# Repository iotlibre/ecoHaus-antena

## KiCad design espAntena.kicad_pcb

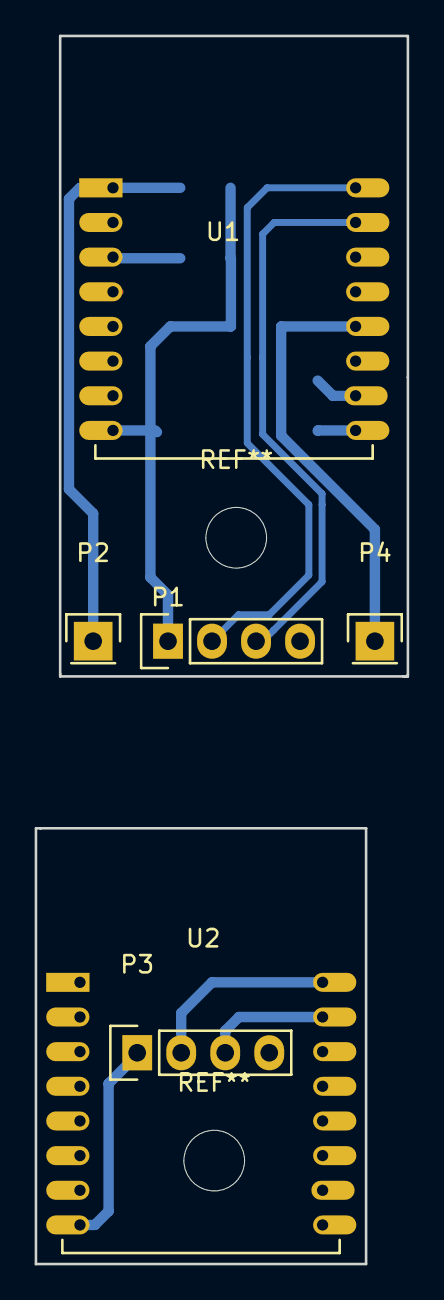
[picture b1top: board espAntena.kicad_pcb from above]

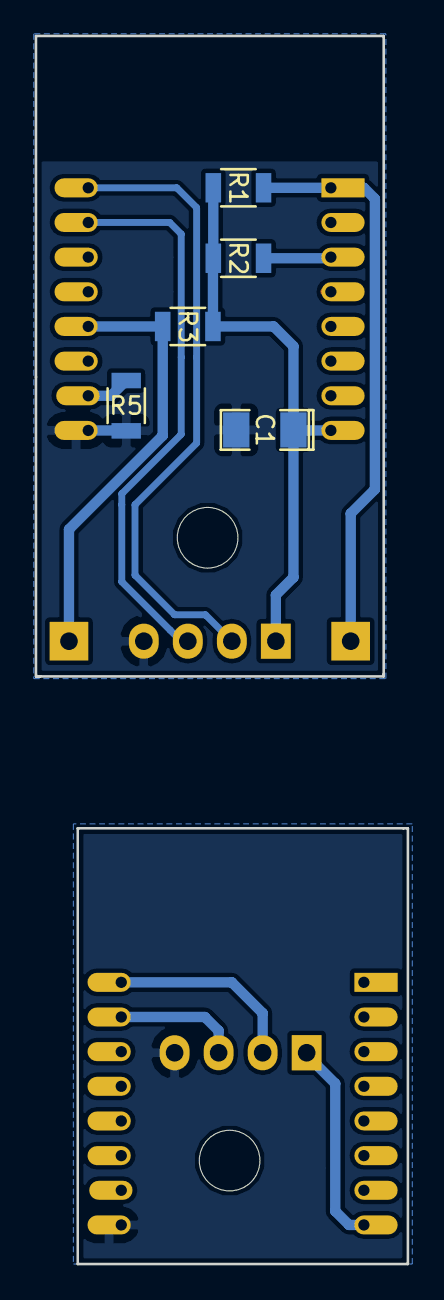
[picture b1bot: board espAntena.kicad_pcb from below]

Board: 2 copper layers, 21.5 x 70.9 mm, 11 parts (5 on the bottom side), 11 nets.

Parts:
C1: 100nF; SMD-1206_Pol
P1, P3: CONN_01X04; Socket_Strip_Straight_1x04
P2, P4: CONN_01X01; Pin_Header_Straight_1x01
R1, R2, R3: 10KR; R_1206
R5: 10kR; R_1206
U1, U2: ESP-12E

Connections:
GND: C1.2, P1.4, P3.4, R5.1, U1.9, U2.9
unnamed: R2.1, U1.3
unnamed: R5.2, U1.10
PRGM: P4.1, R3.2, U1.12
RST: P2.1, R1.1, U1.1
RXD: P1.3, U1.15
RXD_B: P3.3, U2.15
TXD: P1.2, U1.16
TXD_B: P3.2, U2.16
Vcc: C1.1, P1.1, R1.2, R2.2, R3.1, U1.8
Vcc_B: P3.1, U2.8

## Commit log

2018-06-05 primera version
